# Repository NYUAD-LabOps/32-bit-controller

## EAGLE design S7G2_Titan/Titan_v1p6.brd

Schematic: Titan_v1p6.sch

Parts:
AFID1, AFID2, AFID3, AFID4, AFID5, AFID6: FIDUCIAL_1MM
C1, C2: 24pF; 0402
C3: 100pF; 0402
C4, C7, C9, C10, C12, C13, C15, C19, C20, C22, C24, C25, C26, C27, C29, C30, C33, C34, C35, C36, C38, C39, C40, C42, C43: 0.1uF; 0402
C5, C6, C16, C23: 10uF; 0402
C8, C14: 22uF; 0402
C11: 2.2uF; 0402
C17, C18: 18pF; 0402
C21, C28, C41: 1uF; 0402
C31: 10uF_Tant; C1210
C32, C37: 12pF; 0402
FB1: FB2_603; 0603
J1: SD_CARD
J2: 4-pos; 1X4_3.81MM_PITCH
J3, J5, J9: 10-pos; 2X5
J4, J10: 20-pos; 2_X_10_.1_INCH
J6: USB-A; USB_A_SMT
J7: USB-B-Micro; USB_MICRO-B
J8: 40-pos; HEADER_2_X_20_.1_INCH
L1: 2.2uH; 1008
LED1: Green; 0805
R1: 6K49; 0402
R2, R3, R13, R19, R20, R23, R24: 10K0; 0402
R4, R6: 1K5; 0402
R5, R7, R8: 470R0; 0402
R9, R10, R11, R12: 33R0; 0402
R14, R15: 1K0; 0402
R16: 15K0; 0402
R17, R18: 27R0; 0402
R21: 30K0; 0402
R22: 2K2; 0402
RJ1: RJ45; RJ45_TH_ELEC
U1: KSZ8081_QFN_24; QFN-24-M
U2: AP2151DWG-7; SOT-23-5
U3: S7G2LQFP176; LQFP176_24X24
X1: 25MHz; SMD_3225
X2: 24MHz; SMD_3225
X3: 32.768KHz; SMD_X_2_PADS

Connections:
C58: C12.P$1 (1), RJ1.4 (CT1)
C60: C13.P$1 (1), RJ1.5 (CT2)
CRS_DV: R12.P$2 (2), U1.15 (CRS_DV/PHYAD[1:0])
D+: J7.P$3 (D+), R18.P$2 (2)
D-: J7.P$2 (D-), R17.P$2 (2)
ETH: U1.16 (REF_CLK), U3.9 (P7_1)
ETH_CRS_DV: R12.P$1 (1), U3.13 (P7_5)
ETH_IRQ14: R2.P$1 (1), U1.18 (INTRP), U3.159 (P0_10/AN103)
ETH_MDC: R4.P$1 (1), U1.11 (MDC), U3.4 (P4_3)
ETH_MDIO: R6.P$1 (1), U1.10 (MDIO), U3.5 (P4_4)
ETH_RESET: C6.P$1 (1), R3.P$1 (1), U1.24 (!RST), U3.172 (P8_6)
ETH_RXD0: R10.P$1 (1), U3.10 (P7_2)
ETH_RXD1: R9.P$1 (1), U3.11 (P7_3)
ETH_RX_ER: R11.P$1 (1), U3.12 (P7_4)
ETH_TXD0: U1.20 (TXD0), U3.8 (P7_0)
ETH_TXD1: U1.21 (TXD1), U3.7 (P4_6)
ETH_TXD_EN: U1.19 (TXEN), U3.6 (P4_5)
GND: C1.P$2 (2), C2.P$2 (2), C3.P$2 (2), C4.P$2 (2), C5.P$2 (2), C6.P$2 (2), C7.P$2 (2), C8.P$2 (2), C9.P$2 (2), C10.P$2 (2), C11.P$2 (2), C12.P$2 (2), C13.P$2 (2), C14.P$2 (2), C15.P$2 (2), C16.P$2 (2), C17.P$2 (2), C18.P$2 (2), C19.P$1 (1), C20.P$1 (1), C21.P$1 (1), C22.P$1 (1), C23.P$2 (2), C24.P$1 (1), C25.P$1 (1), C26.P$2 (2), C27.P$1 (1), C28.P$2 (2), C29.P$2 (2), C30.P$1 (1), C31.2, C32.P$2 (2), C33.P$2 (2), C34.P$1 (1), C35.P$1 (1), C36.P$2 (2), C37.P$2 (2), C38.P$1 (1), C39.P$2 (2), C40.P$2 (2), C41.P$2 (2), C42.P$2 (2), C43.P$1 (1), J1.6 (SUPPLY_VOLTAGE_GROUND), J2.P$1, J3.6, J3.8, J3.10, J6.GND, J7.P$5 (GND), J8.P$1, J9.2, J9.4, J9.6, J9.8, J9.10, J10.P$19, LED1.2 (C), R1.P$1 (1), R21.P$1 (1), R22.P$1 (1), R23.P$1 (1), R24.P$1 (1), RJ1.8, RJ1.10 (GLO), U1.22 (GND), U1.25, U2.2 (GND), U3.22 (VSS1), U3.28 (AVSS_USBHS), U3.29 (PVSS_USBHS), U3.30 (VSS2_USBHS), U3.33 (VSS1_USBHS), U3.35 (VSSIO), U3.45 (VSS_USB), U3.60 (VSS(IO)2), U3.63 (VSS(IO/DCDC)), U3.66 (VCC_DCDC(IO/DCDC)), U3.83 (VSS(IO)3), U3.98 (VSS(IO)4), U3.111 (VSS(IO)5), U3.124 (VSS(IO)6), U3.139 (VSS(IO)7), U3.150 (VSS(IO)8), U3.153 (VREFL), U3.156 (AVSS0), U3.157 (VREFL0), U3.170 (VSS(IO)9), X1.2, X1.4, X2.2, X2.4
GNDE: J1.S1 (SHIELD), J1.S2 (SHIELD), J1.S3 (SHIELD), J1.S4 (SHIELD), J2.P$4, J6.SHLD1 (SHIELD_1), J6.SHLD2 (SHIELD_2), J7.P$6 (SHIELD1), J7.P$7 (SHIELD2), J7.P$8 (SHIELD3), J7.P$9 (SHIELD4), RJ1.13 (GNDE0), RJ1.14 (GNDE1)
ID: J7.P$4 (ID)
IIC_1_SCL: J8.P$5, R14.P$2 (2), U3.132 (P1_0)
IIC_1_SDA: J8.P$6, R15.P$2 (2), U3.131 (P1_1)
INT_MI_01: J8.P$39, U3.87 (P3_1)
INT_MI_02: J8.P$40, U3.86 (P3_2)
INT_MI_03: J8.P$9, U3.128 (P1_4)
INT_MI_04: J8.P$10, U3.127 (P1_5)
LED1/SPEED: RJ1.11 (YLO), U1.23 (LED0/ANEN_SPEED)
unnamed: C24.P$2 (2), U3.148 (VCL2)
unnamed: LED1.1 (A), R5.P$1 (1)
unnamed: C33.P$1 (1), U3.19 (VCLO)
unnamed: C42.P$1 (1), U3.62 (VCL1)
unnamed: R23.P$2 (2), U3.64 (VLO1(DCDC))
unnamed: R24.P$2 (2), U3.65 (VLO2(DCDC))
unnamed: R22.P$2 (2), U3.27 (USBHS_RREF)
NC: RJ1.7
P0_00: J4.P$2, U3.169 (P0_0/AN0\00)
P0_01: J4.P$1, U3.168 (P0_1/AN001)
P0_02: J5.1, U3.167 (P0_2/AN002)
P0_03: J5.3, U3.166 (P0_3/PGAVSS000)
P0_04: J5.5, U3.165 (P0_4/AN100)
P0_05: J5.7, U3.164 (P0_5/AN101)
P0_06: J5.9, U3.163 (P0_6/AN102)
P0_07: J5.10, U3.162 (P0_7/PGVSS100)
P0_08: J5.8, U3.161 (P0_8/AN003)
P0_09: J5.6, U3.160 (P0_9/AN004)
P0_14: J5.4, U3.152 (P0_14/DA0/AN005/AN105)
P0_15: J5.2, U3.151 (P0_15/DA1/AN006/AN106)
P1_02: J8.P$7, U3.130 (P1_2)
P1_03: J8.P$8, U3.129 (P1_3)
P1_06: J8.P$11, U3.126 (P1_6)
P1_07: J8.P$12, U3.125 (P1_7)
P1_11: J8.P$38, U3.92 (P1_11)
P1_12: J8.P$37, U3.93 (P1_12)
P1_13: J8.P$36, U3.94 (P1_13)
P1_14: J8.P$35, U3.95 (P1_14)
P1_15: J8.P$34, U3.96 (P1_15)
P2_00: J10.P$13, U3.69 (P2_0(INPUT_ONLY))
P2_01: J10.P$14, U3.68 (P2_1/MD)
P2_02: J4.P$9, U3.54 (P2_2)
P2_03: J9.1, U3.53 (P2_3)
P2_04: J9.3, U3.52 (P2_4)
P2_05: J9.5, U3.51 (P2_5)
P2_06: J9.7, U3.50 (P2_6)
P2_07: J9.9, U3.49 (P2_7)
P3_03: J10.P$2, U3.85 (P3_3)
P3_04: J10.P$4, U3.82 (P3_4)
P3_05: J10.P$6, U3.81 (P3_5)
P3_06: J10.P$1, U3.80 (P3_6)
P3_07: J10.P$3, U3.79 (P3_7)
P3_09: J10.P$5, U3.77 (P3_9)
P3_10: J10.P$7, U3.76 (P3_10)
P3_11: J10.P$8, U3.75 (P3_11)
P3_12: J10.P$9, U3.74 (P3_12)
P3_13: J10.P$20, U3.55 (P3_13)
P3_14: J10.P$17, U3.56 (P3_14)
P3_15: J10.P$18, U3.57 (P3_15)
P4_00: J4.P$7, U3.1 (P4_0)
P4_01: J4.P$8, U3.2 (P4_1)
P4_02: U3.3 (P4_2)
P4_08: J4.P$20, U3.43 (P4_8)
P4_09: J4.P$19, U3.42 (P4_9)
P4_10: J4.P$18, U3.41 (P4_10)
P4_11: J4.P$17, U3.40 (P4_11)
P4_12: J4.P$16, U3.39 (P4_12)
P4_13: J4.P$15, U3.38 (P4_13)
P4_14: J4.P$14, U3.37 (P4_14)
P4_15: J4.P$13, U3.36 (P4_15)
P5_11: J4.P$6, U3.176 (P5_11)
P5_12: J4.P$5, U3.175 (P5_12)
P5_13: J4.P$4, U3.174 (P5_13)
P6_00: J8.P$13, U3.122 (P6_0)
P6_01: J8.P$14, U3.121 (P6_1)
P6_02: J8.P$15, U3.120 (P6_2)
P6_03: J8.P$16, U3.119 (P6_3)
P6_04: J8.P$17, U3.118 (P6_4)
P6_05: J8.P$18, U3.117 (P6_5)
P6_06: J8.P$19, U3.116 (P6_6)
P6_07: J8.P$20, U3.115 (P6_7)
P6_08: J8.P$33, U3.99 (P6_8)
P6_09: J8.P$32, U3.100 (P6_9)
P6_10: J8.P$31, U3.101 (P6_10)
P6_11: J8.P$30, U3.102 (P6_11)
P6_12: J8.P$29, U3.103 (P6_12)
P6_13: J8.P$28, U3.104 (P6_13)
P6_14: J8.P$27, U3.105 (P6_14)
P6_15: J8.P$26, U3.106 (P6_15)
P7_06: J4.P$10, U3.14 (P7_6)
P7_07: J4.P$11, U3.15 (P7_7)
P8_00: J8.P$4, U3.133 (P8_0)
P8_01: J8.P$3, U3.134 (P8_1)
P8_02: J8.P$2, U3.135 (P8_2)
P8_03: U3.136 (P8_3)
P8_04: U3.137 (P8_4)
P8_05: J4.P$3, U3.173 (P8_5)
P9_00: J10.P$16, U3.58 (P9_0)
P9_01: J10.P$15, U3.59 (P9_1)
P9_05: J10.P$10, U3.73 (P9_5)
P9_06: J10.P$11, U3.72 (P9_6)
P9_07: J10.P$12, U3.71 (P9_7)
P9_08: U3.70 (P9_8)
PA_00: J8.P$21, U3.114 (PA_0)
PA_01: J8.P$22, U3.113 (PA_1)
PA_08: J8.P$25, U3.107 (PA_8)
PA_09: J8.P$24, U3.108 (PA_9)
PA_10: J8.P$23, U3.109 (PA_10)
PB_00: J4.P$12, U3.16 (PB_0)
R51: R7.P$1 (1), RJ1.12 (YHI)
R52: R8.P$1 (1), RJ1.9 (GHI)
RESET: C16.P$1 (1), J3.9, R13.P$1 (1), U3.67 (RES#)
REXT: C3.P$1 (1), R1.P$2 (2), U1.9 (REXT)
RXD0: R10.P$2 (2), U1.13 (RXD0)
RXD1: R9.P$2 (2), U1.12 (RXD1)
RXER: R11.P$2 (2), U1.17 (RXER)
RXM: RJ1.6 (RD-), U1.3 (RXM)
RXP: RJ1.3 (RD+), U1.4 (RXP)
SD1_CD: J1.10 (CD_SWITCH2), U3.146 (P5_6/AN019)
SD1_CLK: J1.5 (CLOCK), U3.140 (P5_0/AN016)
SD1_CMD: J1.3 (COMMAND/RESPONSE), U3.141 (P5_1/AN116)
SD1_DAT0: J1.7 (DATA_LINE[BIT_0]), U3.142 (P5_2/AN017)
SD1_DAT1: J1.8 (DATA_LINE[BIT_1]), U3.143 (P5_3/AN117)
SD1_DAT2: J1.1 (DATA_LINE[BIT_2]), U3.144 (P5_4/AN018)
SD1_DAT3: J1.2 (CARD_DETECT/DATA_LINE[BIT_3]), U3.145 (P5_5/AN118)
SD1_WP: J1.9 (CD_SWITCH1), U3.147 (P5_7/AN119)
TCK: J3.7, U3.88 (P3_0)
TDI: J3.1, U3.91 (P1_10)
TDO: J3.3, U3.90 (P1_9)
TMS: J3.5, U3.89 (P1_8)
TXM: RJ1.2 (TD-), U1.5 (TXM)
TXP: RJ1.1 (TD+), U1.6 (TXP)
USBHS_FAULT: R19.P$1 (1), U2.3 (FLG), U3.78 (P3_8)
USBHS_N: J6.D-, U3.31 (USBHS_DM)
USBHS_P: J6.D+, U3.32 (USBHS_DP)
USBHS_VBUS: C29.P$1 (1), C31.1, J6.VBUS, U2.5 (OUT), U3.17 (PB_1)
USBHS_VBUSEN: R20.P$1 (1), U2.1 (EN)
USB_N: R17.P$1 (1), U3.46 (USB_DM)
USB_P: R18.P$1 (1), U3.47 (USB_DP)
USB_VBUS_B: R16.P$1 (1), U3.44 (P4_7)
VBUS: C28.P$1 (1), J7.P$1 (VBUS), R16.P$2 (2), R21.P$2 (2)
VCL_F(FLASH): C34.P$2 (2), U3.112 (VCL_F(FLASH))
VDD: C4.P$1 (1), C5.P$1 (1), C7.P$1 (1), C14.P$1 (1), C15.P$1 (1), C19.P$2 (2), C20.P$2 (2), C21.P$2 (2), C22.P$2 (2), C25.P$2 (2), C27.P$2 (2), C30.P$2 (2), C35.P$2 (2), C36.P$1 (1), C38.P$2 (2), C39.P$1 (1), C40.P$1 (1), C41.P$1 (1), C43.P$2 (2), FB1.1, J1.4 (SUPPLY_VOLTAGE), J3.2, J3.4, L1.2, R2.P$2 (2), R3.P$2 (2), R4.P$2 (2), R5.P$2 (2), R6.P$2 (2), R7.P$2 (2), R8.P$2 (2), R13.P$2 (2), R14.P$1 (1), R15.P$1 (1), U1.14 (VDDIO), U3.25 (VCC1), U3.26 (AVCC_SUBHS), U3.34 (VCC_USBHS), U3.48 (VCC_USB), U3.61 (VCC(IO)2), U3.84 (VCC(IO)3), U3.97 (VCC(IO)4), U3.110 (VCC(IO)5), U3.123 (VCC(IO)6), U3.138 (VCC(IO)7), U3.149 (VCC(IO)8), U3.154 (VREFH), U3.155 (AVCC0), U3.158 (VREFH0), U3.171 (VCC(IO)9)
VDD5: C23.P$1 (1), C26.P$1 (1), J2.P$3, R19.P$2 (2), R20.P$2 (2), U2.4 (VIN)
VDDIN: J2.P$2, L1.1
VDD_1.2: C10.P$1 (1), C11.P$1 (1), U1.1 (VDD_1.2)
VDD_ENET1: C8.P$1 (1), C9.P$1 (1), FB1.2, U1.2 (VDDA_3.3)
XCIN: C32.P$1 (1), U3.20 (XCIN), X3.P$1
XCOUT: C37.P$1 (1), U3.21 (XCOUT), X3.P$2
XII: C1.P$1 (1), U1.8 (XI), X1.1
XOO: C2.P$1 (1), U1.7 (XO), X1.3
XTAL1: C17.P$1 (1), U3.23 (P2_13/XTAL), X2.1
XTAL2: C18.P$1 (1), U3.24 (P2_12/EXTAL), X2.3

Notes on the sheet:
Power Input
JTAG

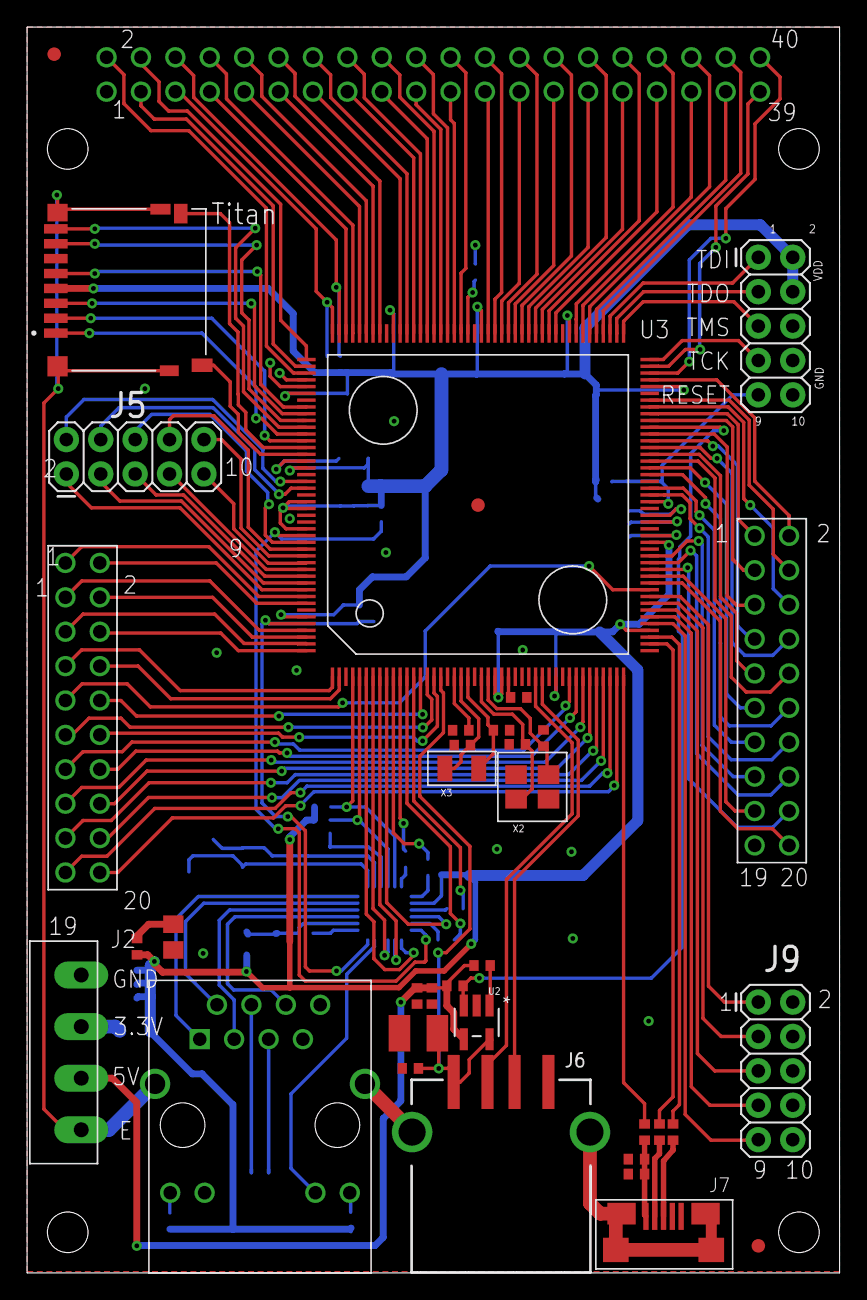
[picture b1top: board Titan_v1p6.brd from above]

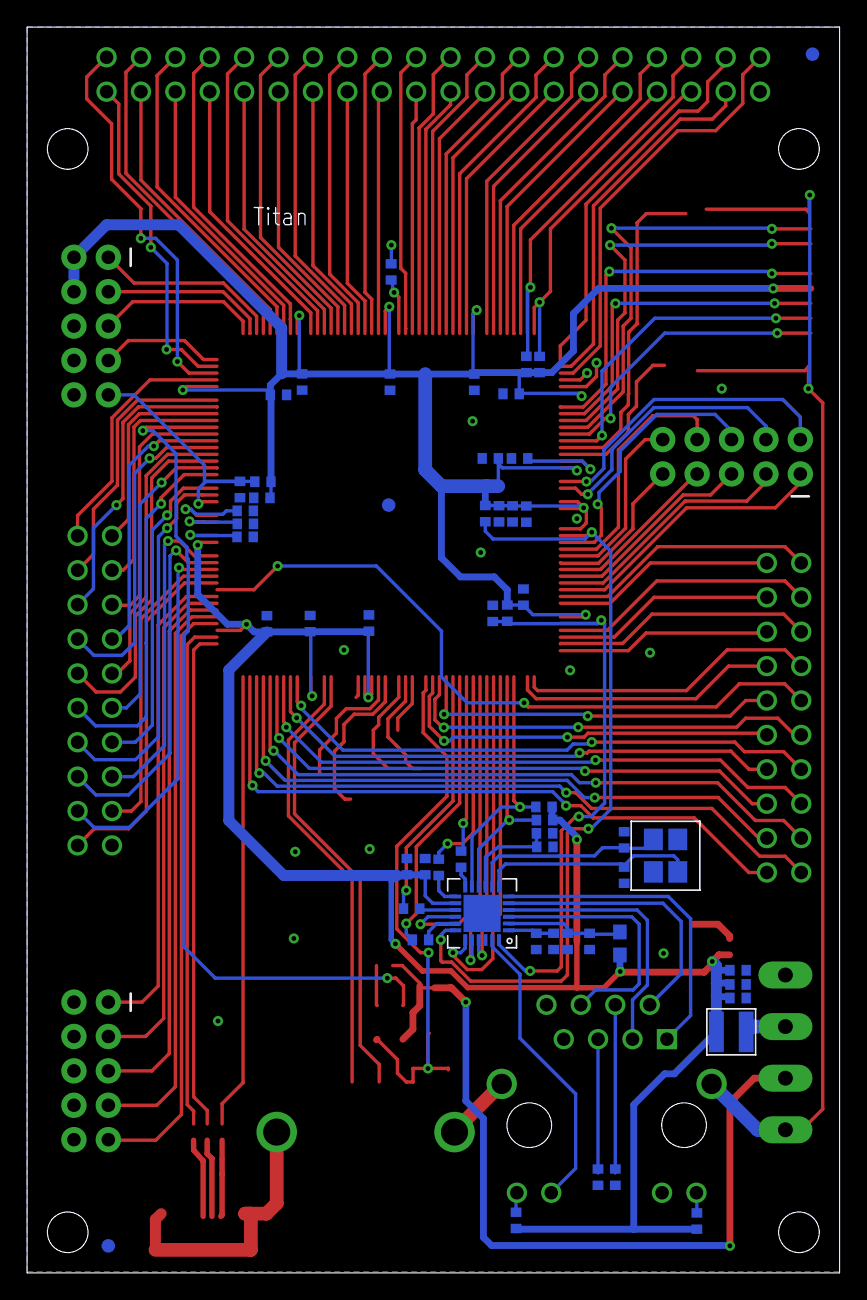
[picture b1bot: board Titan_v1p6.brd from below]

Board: 2 copper layers, 60.0 x 92.0 mm, 93 parts (56 on the bottom side), 164 nets.

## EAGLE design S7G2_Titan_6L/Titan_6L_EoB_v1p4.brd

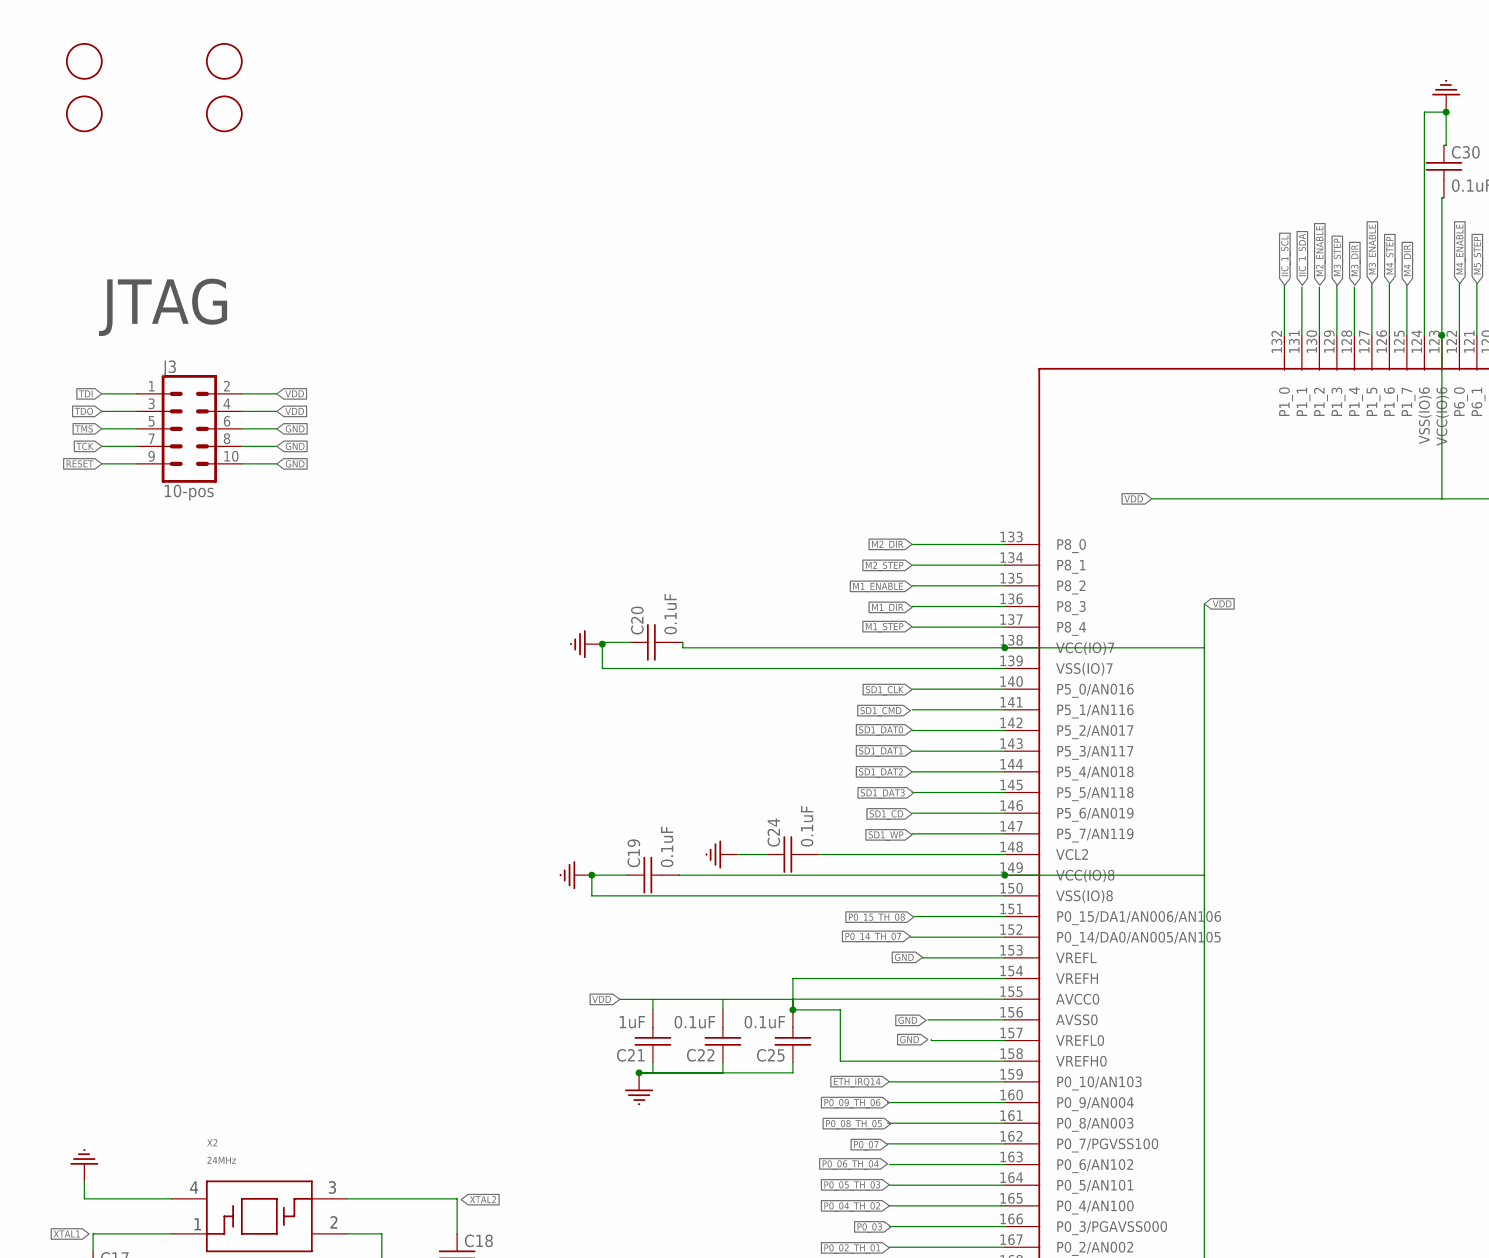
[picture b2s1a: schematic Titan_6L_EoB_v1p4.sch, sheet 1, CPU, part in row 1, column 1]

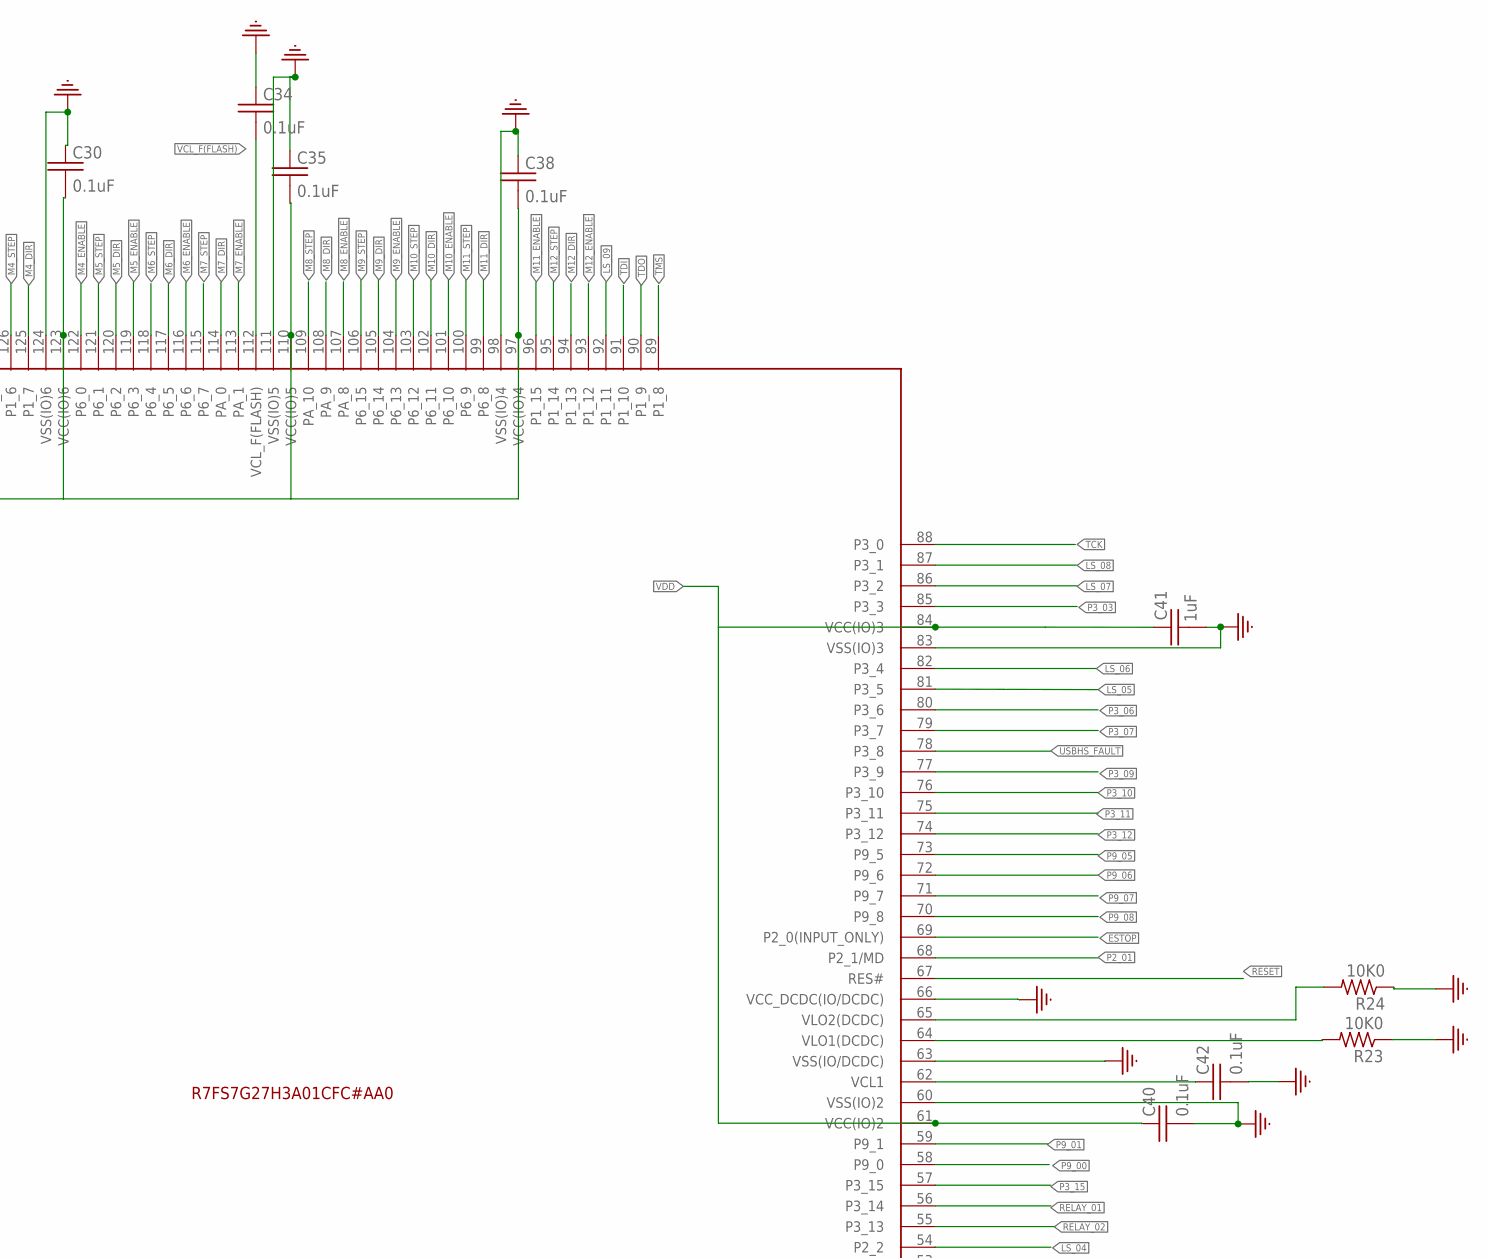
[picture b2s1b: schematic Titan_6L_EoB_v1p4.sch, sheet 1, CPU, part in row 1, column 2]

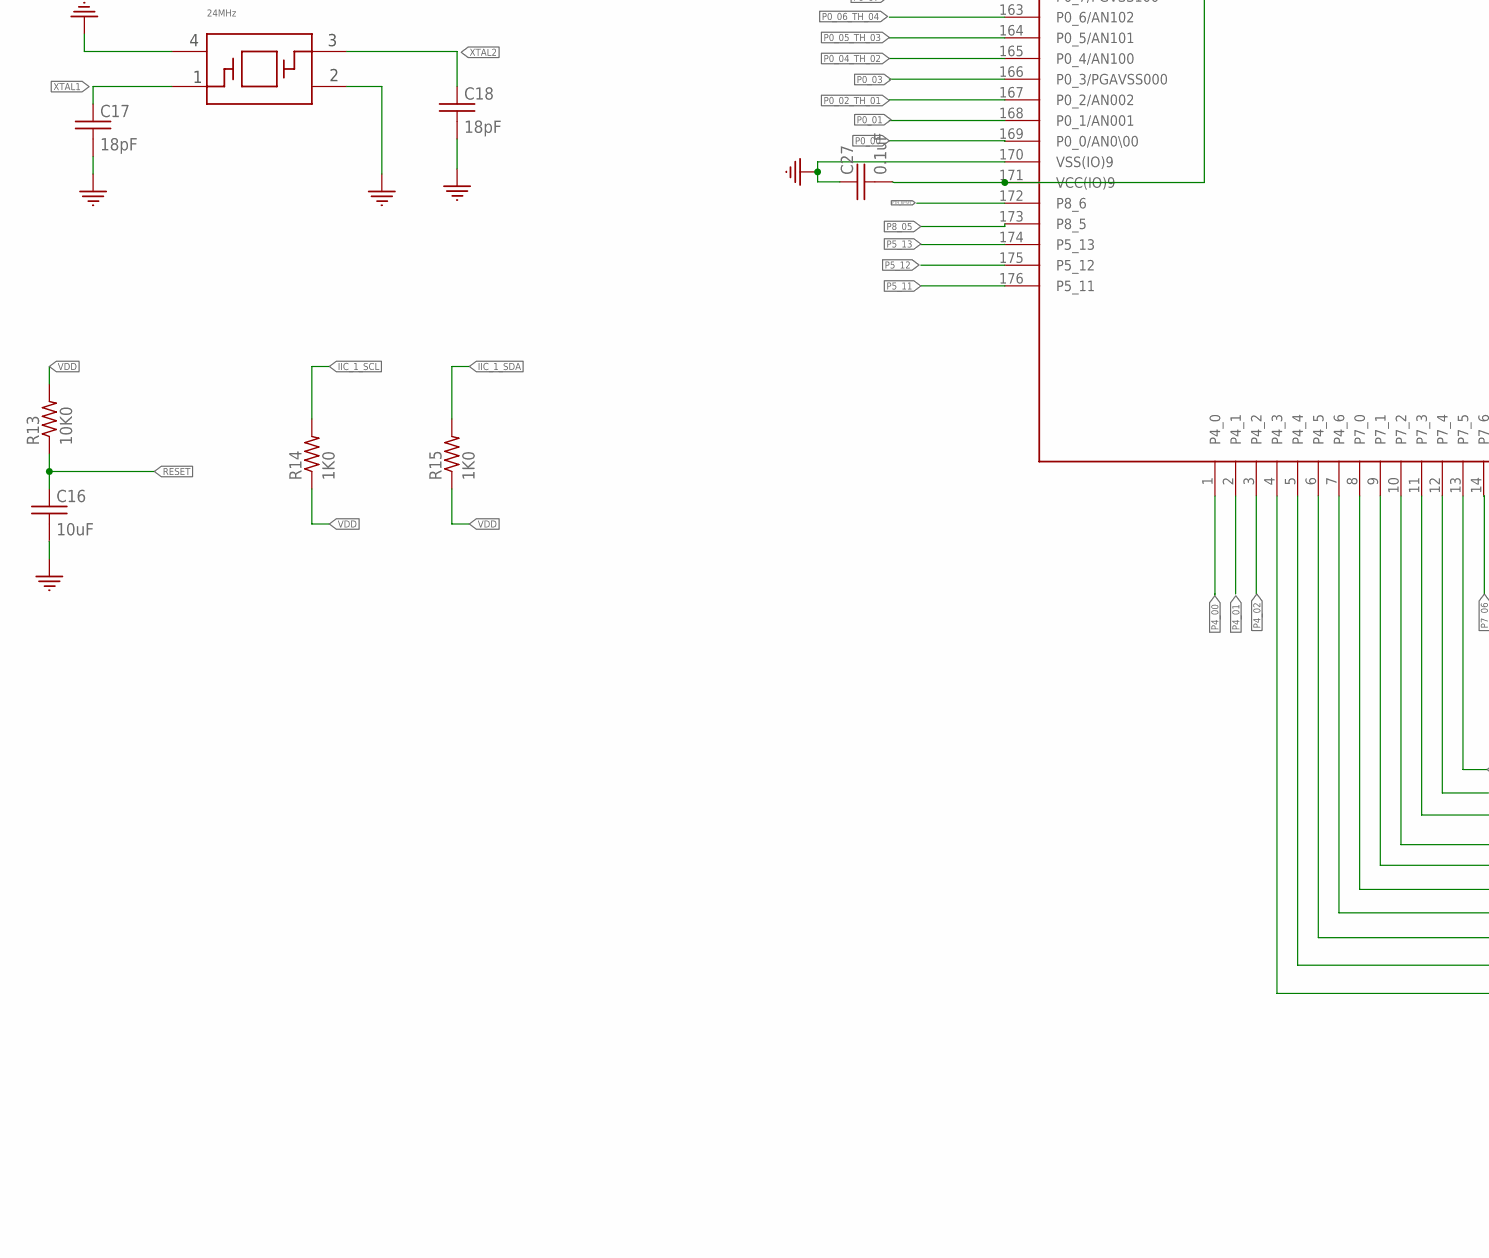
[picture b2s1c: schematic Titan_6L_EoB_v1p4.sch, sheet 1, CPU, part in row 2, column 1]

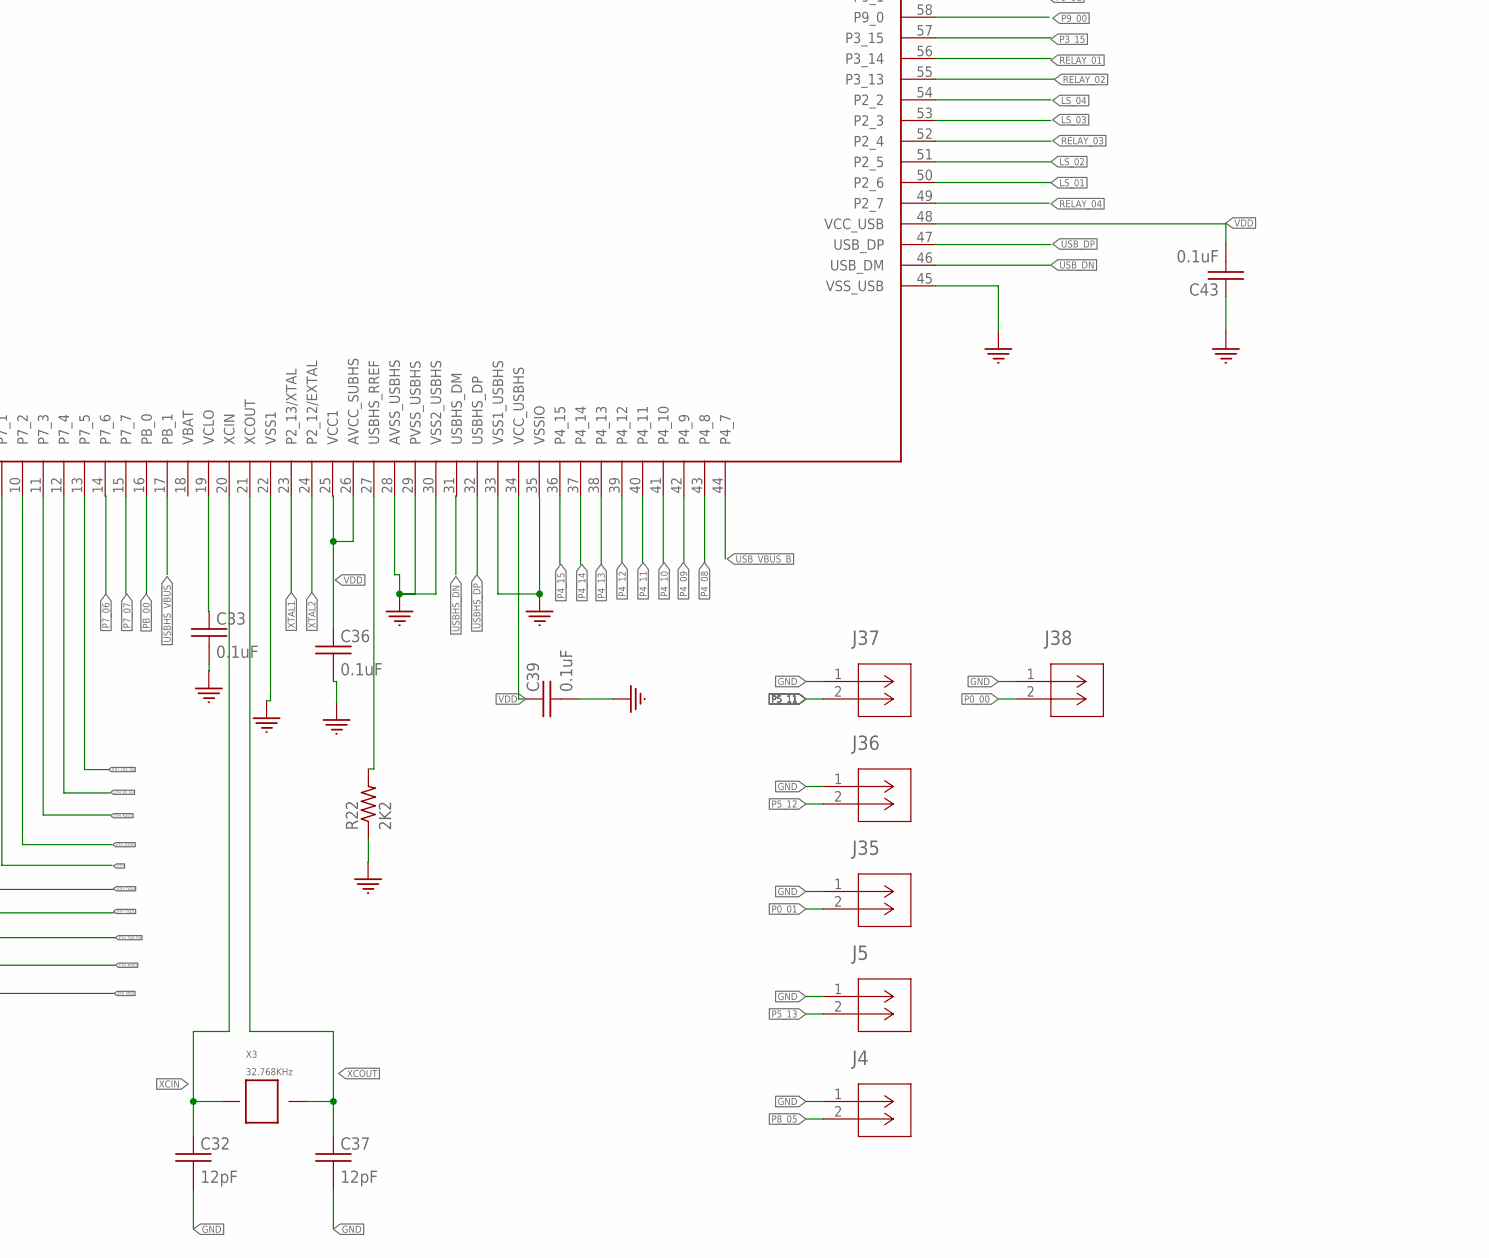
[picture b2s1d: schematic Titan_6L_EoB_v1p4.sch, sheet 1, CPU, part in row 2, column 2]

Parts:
AFID1, AFID2, AFID4, AFID5: FIDUCIAL_1MM
C16: 10uF; 0402
C17, C18: 18pF; 0402
C19, C20, C22, C24, C25, C27, C30, C33, C34, C35, C36, C38, C39, C40, C42, C43: 0.1uF; 0402
C21, C41: 1uF; 0402
C32, C37: 12pF; 0402
J3: 10-pos; 2X5
J4, J5, J35, J36, J37, J38: CONN_530470210_PICOBLADE_X_2; CON_530470210_MOL
R13, R23, R24: 10K0; 0402
R14, R15: 1K0; 0402
R22: 2K2; 0402
U3: S7G2LQFP176; LQFP176_24X24
X2: 24MHz; SMD_3225
X3: 32.768KHz; SMD_X_2_PADS

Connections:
ESTOP: U3.69 (P2_0(INPUT_ONLY)); also elsewhere on the board
ETH_CLK: U3.9 (P7_1); also elsewhere on the board
ETH_CRS_DV: U3.13 (P7_5); also elsewhere on the board
ETH_IRQ14: U3.159 (P0_10/AN103); also elsewhere on the board
ETH_MDC: U3.4 (P4_3); also elsewhere on the board
ETH_MDIO: U3.5 (P4_4); also elsewhere on the board
ETH_RESET: U3.172 (P8_6); also elsewhere on the board
ETH_RXD0: U3.10 (P7_2); also elsewhere on the board
ETH_RXD1: U3.11 (P7_3); also elsewhere on the board
ETH_RX_ER: U3.12 (P7_4); also elsewhere on the board
ETH_TXD0: U3.8 (P7_0); also elsewhere on the board
ETH_TXD1: U3.7 (P4_6); also elsewhere on the board
ETH_TXD_EN: U3.6 (P4_5); also elsewhere on the board
GND: C16.P$2 (2), C17.P$2 (2), C18.P$2 (2), C19.P$1 (1), C20.P$1 (1), C21.P$1 (1), C22.P$1 (1), C24.P$1 (1), C25.P$1 (1), C27.P$1 (1), C30.P$1 (1), C32.P$2 (2), C33.P$2 (2), C34.P$1 (1), C35.P$1 (1), C36.P$2 (2), C37.P$2 (2), C38.P$1 (1), C39.P$2 (2), C40.P$2 (2), C41.P$2 (2), C42.P$2 (2), C43.P$1 (1), J3.6, J3.8, J3.10, J4.1, J5.1, J35.1, J36.1, J37.1, J38.1, R22.P$1 (1), R23.P$1 (1), R24.P$1 (1), U3.22 (VSS1), U3.28 (AVSS_USBHS), U3.29 (PVSS_USBHS), U3.30 (VSS2_USBHS), U3.33 (VSS1_USBHS), U3.35 (VSSIO), U3.45 (VSS_USB), U3.60 (VSS(IO)2), U3.63 (VSS(IO/DCDC)), U3.66 (VCC_DCDC(IO/DCDC)), U3.83 (VSS(IO)3), U3.98 (VSS(IO)4), U3.111 (VSS(IO)5), U3.124 (VSS(IO)6), U3.139 (VSS(IO)7), U3.150 (VSS(IO)8), U3.153 (VREFL), U3.156 (AVSS0), U3.157 (VREFL0), U3.170 (VSS(IO)9), X2.2, X2.4; also elsewhere on the board
IIC_1_SCL: R14.P$2 (2), U3.132 (P1_0)
IIC_1_SDA: R15.P$2 (2), U3.131 (P1_1)
LS_01: U3.50 (P2_6); also elsewhere on the board
LS_02: U3.51 (P2_5); also elsewhere on the board
LS_03: U3.53 (P2_3); also elsewhere on the board
LS_04: U3.54 (P2_2); also elsewhere on the board
LS_05: U3.81 (P3_5); also elsewhere on the board
LS_06: U3.82 (P3_4); also elsewhere on the board
LS_07: U3.86 (P3_2); also elsewhere on the board
LS_08: U3.87 (P3_1); also elsewhere on the board
LS_09: U3.92 (P1_11); also elsewhere on the board
M1_DIR: U3.136 (P8_3); also elsewhere on the board
M1_ENABLE: U3.135 (P8_2); also elsewhere on the board
M1_STEP: U3.137 (P8_4); also elsewhere on the board
M2_DIR: U3.133 (P8_0); also elsewhere on the board
M2_ENABLE: U3.130 (P1_2); also elsewhere on the board
M2_STEP: U3.134 (P8_1); also elsewhere on the board
M3_DIR: U3.128 (P1_4); also elsewhere on the board
M3_ENABLE: U3.127 (P1_5); also elsewhere on the board
M3_STEP: U3.129 (P1_3); also elsewhere on the board
M4_DIR: U3.125 (P1_7); also elsewhere on the board
M4_ENABLE: U3.122 (P6_0); also elsewhere on the board
M4_STEP: U3.126 (P1_6); also elsewhere on the board
M5_DIR: U3.120 (P6_2); also elsewhere on the board
M5_ENABLE: U3.119 (P6_3); also elsewhere on the board
M5_STEP: U3.121 (P6_1); also elsewhere on the board
M6_DIR: U3.117 (P6_5); also elsewhere on the board
M6_ENABLE: U3.116 (P6_6); also elsewhere on the board
M6_STEP: U3.118 (P6_4); also elsewhere on the board
M7_DIR: U3.114 (PA_0); also elsewhere on the board
M7_ENABLE: U3.113 (PA_1); also elsewhere on the board
M7_STEP: U3.115 (P6_7); also elsewhere on the board
M8_DIR: U3.108 (PA_9); also elsewhere on the board
M8_ENABLE: U3.107 (PA_8); also elsewhere on the board
M8_STEP: U3.109 (PA_10); also elsewhere on the board
M9_DIR: U3.105 (P6_14); also elsewhere on the board
M9_ENABLE: U3.104 (P6_13); also elsewhere on the board
M9_STEP: U3.106 (P6_15); also elsewhere on the board
M10_DIR: U3.102 (P6_11); also elsewhere on the board
M10_ENABLE: U3.101 (P6_10); also elsewhere on the board
M10_STEP: U3.103 (P6_12); also elsewhere on the board
M11_DIR: U3.99 (P6_8); also elsewhere on the board
M11_ENABLE: U3.96 (P1_15); also elsewhere on the board
M11_STEP: U3.100 (P6_9); also elsewhere on the board
M12_DIR: U3.94 (P1_13); also elsewhere on the board
M12_ENABLE: U3.93 (P1_12); also elsewhere on the board
M12_STEP: U3.95 (P1_14); also elsewhere on the board
unnamed: C24.P$2 (2), U3.148 (VCL2)
unnamed: C33.P$1 (1), U3.19 (VCLO)
unnamed: C42.P$1 (1), U3.62 (VCL1)
unnamed: R23.P$2 (2), U3.64 (VLO1(DCDC))
unnamed: R24.P$2 (2), U3.65 (VLO2(DCDC))
unnamed: R22.P$2 (2), U3.27 (USBHS_RREF)
P0_00: J38.2, U3.169 (P0_0/AN0\00)
P0_01: J35.2, U3.168 (P0_1/AN001)
P0_02_TH_01: U3.167 (P0_2/AN002); also elsewhere on the board
P0_03: U3.166 (P0_3/PGAVSS000)
P0_04_TH_02: U3.165 (P0_4/AN100); also elsewhere on the board
P0_05_TH_03: U3.164 (P0_5/AN101); also elsewhere on the board
P0_06_TH_04: U3.163 (P0_6/AN102); also elsewhere on the board
P0_07: U3.162 (P0_7/PGVSS100)
P0_08_TH_05: U3.161 (P0_8/AN003); also elsewhere on the board
P0_09_TH_06: U3.160 (P0_9/AN004); also elsewhere on the board
P0_14_TH_07: U3.152 (P0_14/DA0/AN005/AN105); also elsewhere on the board
P0_15_TH_08: U3.151 (P0_15/DA1/AN006/AN106); also elsewhere on the board
P2_01: U3.68 (P2_1/MD)
P3_03: U3.85 (P3_3)
P3_06: U3.80 (P3_6)
P3_07: U3.79 (P3_7)
P3_09: U3.77 (P3_9)
P3_10: U3.76 (P3_10); also elsewhere on the board
P3_11: U3.75 (P3_11); also elsewhere on the board
P3_12: U3.74 (P3_12); also elsewhere on the board
P3_15: U3.57 (P3_15); also elsewhere on the board
P4_00: U3.1 (P4_0)
P4_01: U3.2 (P4_1)
P4_02: U3.3 (P4_2)
P4_08: U3.43 (P4_8)
P4_09: U3.42 (P4_9)
P4_10: U3.41 (P4_10)
P4_11: U3.40 (P4_11)
P4_12: U3.39 (P4_12)
P4_13: U3.38 (P4_13)
P4_14: U3.37 (P4_14)
P4_15: U3.36 (P4_15)
P5_11: J37.2, U3.176 (P5_11)
P5_12: J36.2, U3.175 (P5_12)
P5_13: J5.2, U3.174 (P5_13)
P7_06: U3.14 (P7_6)
P7_07: U3.15 (P7_7)
P8_05: J4.2, U3.173 (P8_5)
P9_00: U3.58 (P9_0); also elsewhere on the board
P9_01: U3.59 (P9_1); also elsewhere on the board
P9_05: U3.73 (P9_5); also elsewhere on the board
P9_06: U3.72 (P9_6); also elsewhere on the board
P9_07: U3.71 (P9_7); also elsewhere on the board
P9_08: U3.70 (P9_8); also elsewhere on the board
PB_00: U3.16 (PB_0)
RELAY_01: U3.56 (P3_14); also elsewhere on the board
RELAY_02: U3.55 (P3_13); also elsewhere on the board
RELAY_03: U3.52 (P2_4); also elsewhere on the board
RELAY_04: U3.49 (P2_7); also elsewhere on the board
RESET: C16.P$1 (1), J3.9, R13.P$1 (1), U3.67 (RES#)
SD1_CD: U3.146 (P5_6/AN019); also elsewhere on the board
SD1_CLK: U3.140 (P5_0/AN016); also elsewhere on the board
SD1_CMD: U3.141 (P5_1/AN116); also elsewhere on the board
SD1_DAT0: U3.142 (P5_2/AN017); also elsewhere on the board
SD1_DAT1: U3.143 (P5_3/AN117); also elsewhere on the board
SD1_DAT2: U3.144 (P5_4/AN018); also elsewhere on the board
SD1_DAT3: U3.145 (P5_5/AN118); also elsewhere on the board
SD1_WP: U3.147 (P5_7/AN119); also elsewhere on the board
TCK: J3.7, U3.88 (P3_0)
TDI: J3.1, U3.91 (P1_10)
TDO: J3.3, U3.90 (P1_9)
TMS: J3.5, U3.89 (P1_8)
USBHS_DN: U3.31 (USBHS_DM); also elsewhere on the board
USBHS_DP: U3.32 (USBHS_DP); also elsewhere on the board
USBHS_FAULT: U3.78 (P3_8); also elsewhere on the board
USBHS_VBUS: U3.17 (PB_1); also elsewhere on the board
USB_DN: U3.46 (USB_DM); also elsewhere on the board
USB_DP: U3.47 (USB_DP); also elsewhere on the board
USB_VBUS_B: U3.44 (P4_7); also elsewhere on the board
VCL_F(FLASH): C34.P$2 (2), U3.112 (VCL_F(FLASH))
VDD: C19.P$2 (2), C20.P$2 (2), C21.P$2 (2), C22.P$2 (2), C25.P$2 (2), C27.P$2 (2), C30.P$2 (2), C35.P$2 (2), C36.P$1 (1), C38.P$2 (2), C39.P$1 (1), C40.P$1 (1), C41.P$1 (1), C43.P$2 (2), J3.2, J3.4, R13.P$2 (2), R14.P$1 (1), R15.P$1 (1), U3.25 (VCC1), U3.26 (AVCC_SUBHS), U3.34 (VCC_USBHS), U3.48 (VCC_USB), U3.61 (VCC(IO)2), U3.84 (VCC(IO)3), U3.97 (VCC(IO)4), U3.110 (VCC(IO)5), U3.123 (VCC(IO)6), U3.138 (VCC(IO)7), U3.149 (VCC(IO)8), U3.154 (VREFH), U3.155 (AVCC0), U3.158 (VREFH0), U3.171 (VCC(IO)9); also elsewhere on the board
XCIN: C32.P$1 (1), U3.20 (XCIN), X3.P$1
XCOUT: C37.P$1 (1), U3.21 (XCOUT), X3.P$2
XTAL1: C17.P$1 (1), U3.23 (P2_13/XTAL), X2.1
XTAL2: C18.P$1 (1), U3.24 (P2_12/EXTAL), X2.3

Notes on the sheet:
JTAG

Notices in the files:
parts and their libraries:
COPYRIGHT: Copyright (C) 2022 Ultra Librarian. All rights reserved.
COPYRIGHT: Copyright (C) 2023 Ultra Librarian. All rights reserved.
